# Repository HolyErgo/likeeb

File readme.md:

# LIKEeb

### 36-key split wireless keyboard

## Features
- 3x5 key matrix + 3 thumb keys
- highly staggered columns
- rotated pinky and ring columns
- dactyl-like curved columns (not rows)
- Xiao BLE wireless controllers
- hotswap Gateron and Choc V2 switches
- 400mAh battery lasts month or more
- integrated 50-mm magnetic ring
- 2-color case
- magnetic spacer
- no RGB, ergonomics only
- [height-adapted DES-profile keycaps](https://github.com/HolyErgo/DES-MX-low-profile)
- [ZMK firmware](https://github.com/HolyErgo/zmk-likeeb)

## Comfort and Ergonomics

The curve, stagger, and rotation of the columns provide maximum ergonomics. All keys are easily pressed without moving the base of the hand (for M-L hand size).

Thanks to the low profile, the keyboard is comfortable to use without wrist rests and tents.

Placing the controller under the palm allows for convenient keyboard positioning on either side of a laptop, even on a small café table.

400mAh battery lasts more than a month. I haven’t been able to measure exactly how long, because I always forget when I last charged it :) With the new ZMK firmware using Bluetooth Low Energy protocol, one charge might last 3-4 months.

## Integrated Magnetic Ring

It’s very convenient for designing various mounts. You only need to attach a 0.6mm thick metal ring to the mount. Compared to a magnetic mount, this ring is very thin and much cheaper.

For example, I made a mount for an IKEA garden chair that is only 2mm thick. I simply attached it to the armrest of the chair and created a comfortable workspace: [IKEA chair holder.stl](./case/rev2.0/IKEA%20chair%20holder.stl)

## Convenient Transportation

The magnetic spacer connects two halves of the keyboard and protects the keys from accidental presses. I don’t even turn off the keyboard when I put it in my backpack.

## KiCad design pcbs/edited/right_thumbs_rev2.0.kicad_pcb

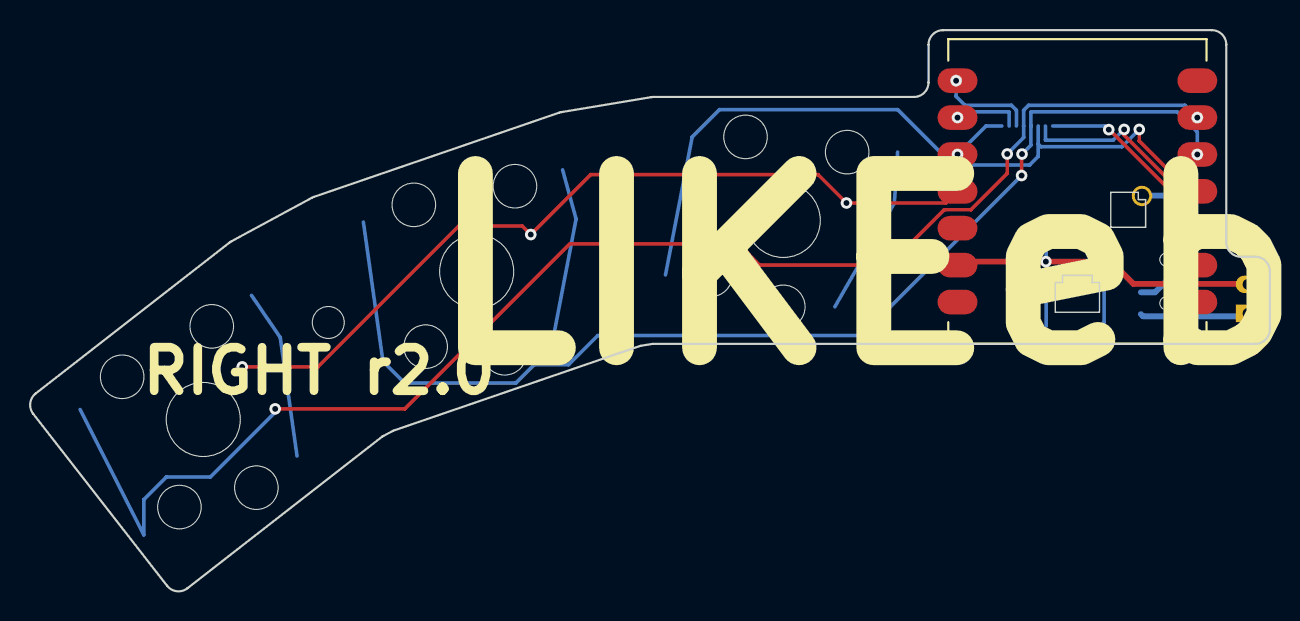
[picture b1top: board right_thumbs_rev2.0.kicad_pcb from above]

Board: 2 copper layers, 85.4 x 38.6 mm, 8 parts (1 on the bottom side), 12 nets.

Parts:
B1: SW_TACT_ALPS_SKQGABE010
BAT1: BatteryPad
S1, S2, S3: KS33PG1353
_1: Seeeduino XIAO nRF52840
_2: HKW FPC Socket
_3: MountingHole_2.2mm_M2_Pad_Via

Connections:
C6: S3.1, S3.2, _1.6, _2.4
C7: S2.1, S2.2, _1.5, _2.5
C8: S1.1, S1.2, _1.4, _2.6
C9: _1.3, _2.7
C10: _1.2, _2.8
GND: B1.1, BAT1.2, _1.13
R1: _1.8, _2.3
R2: _1.9, _2.2
R3: _1.10, _2.1
S1_s2d: S1.1, S1.2
S2_s2d: S2.1, S2.2
S3_s2d: S3.1, S3.2

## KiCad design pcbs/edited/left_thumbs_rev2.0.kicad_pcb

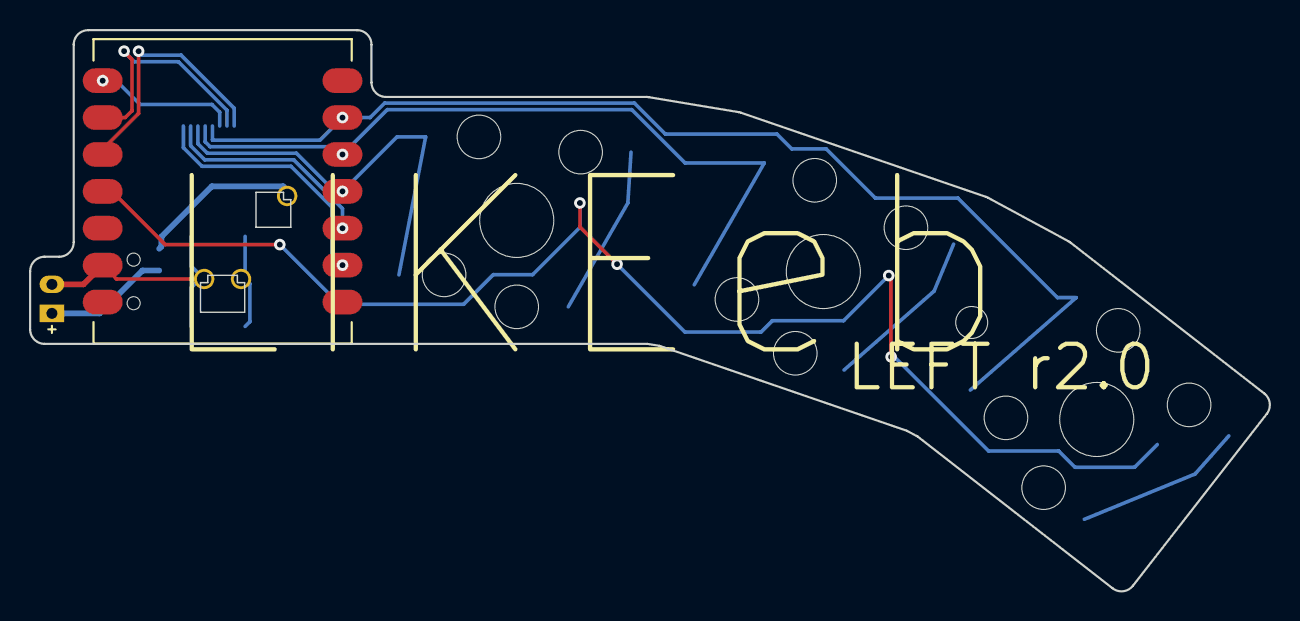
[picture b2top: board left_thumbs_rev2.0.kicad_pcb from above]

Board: 2 copper layers, 85.4 x 38.6 mm, 8 parts (1 on the bottom side), 12 nets.

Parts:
B1: SW_TACT_ALPS_SKQGABE010
BAT1: BatteryPad
S1, S2, S3: KS33PG1353
_1: Seeeduino XIAO nRF52840
_2: HKW FPC Socket
_3: MountingHole_2.2mm_M2_Pad_Via

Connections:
C1: _1.2, _2.1
C2: _1.3, _2.2
C3: S1.1, S1.2, _1.4, _2.3
C4: S2.1, S2.2, _1.5, _2.4
C5: S3.1, S3.2, _1.6, _2.5
GND: B1.1, BAT1.2, _1.13
R1: _1.8, _2.6
R2: _1.9, _2.7
R3: _1.10, _2.8
S1_s2d: S1.1, S1.2
S2_s2d: S2.1, S2.2
S3_s2d: S3.1, S3.2

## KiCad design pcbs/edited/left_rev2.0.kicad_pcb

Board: 2 copper layers, 16 parts (1 on the bottom side), 20 nets.

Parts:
S1, S2, S3, S4, S5, S6, S7, S8, S9, S10, S11, S12, S13, S14, S15: KS33PG1353
_1: HKW FPC Socket

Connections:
C1: S1.1, S1.2, S2.1, S2.2, S3.1, S3.2, _1.8
C2: S4.1, S4.2, S5.1, S5.2, S6.1, S6.2, _1.7
C3: S7.1, S7.2, S8.1, S8.2, S9.1, S9.2, _1.6
C4: S10.1, S10.2, S11.1, S11.2, S15.1, S15.2, _1.5
C4_R2: S15.1, S15.2
C5: S12.1, S12.2, S13.1, S13.2, S14.1, S14.2, _1.4
S1_s2d: S1.1, S1.2
S2_s2d: S2.1, S2.2
S3_s2d: S3.1, S3.2
S4_s2d: S4.1, S4.2
S5_s2d: S5.1, S5.2
S6_s2d: S6.1, S6.2
S7_s2d: S7.1, S7.2
S8_s2d: S8.1, S8.2
S9_s2d: S9.1, S9.2
S10_s2d: S10.1, S10.2
S11_s2d: S11.1, S11.2
S12_s2d: S12.1, S12.2
S13_s2d: S13.1, S13.2
S14_s2d: S14.1, S14.2

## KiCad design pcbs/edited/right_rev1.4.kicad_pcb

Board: 2 copper layers, 16 parts (1 on the bottom side), 5 nets.

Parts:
S1, S2, S3, S4, S5, S6, S7, S8, S9, S10, S11, S12, S13, S14, S15: PG1353
_1: HKW FPC Socket

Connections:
C6: S13.1, S14.1, S15.1, _1.5
C7: S10.1, S11.1, S12.1, _1.4
C8: S7.1, S8.1, S9.1, _1.3
C9: S4.1, S5.1, S6.1, _1.2
C10: S1.1, S2.1, S3.1, _1.1

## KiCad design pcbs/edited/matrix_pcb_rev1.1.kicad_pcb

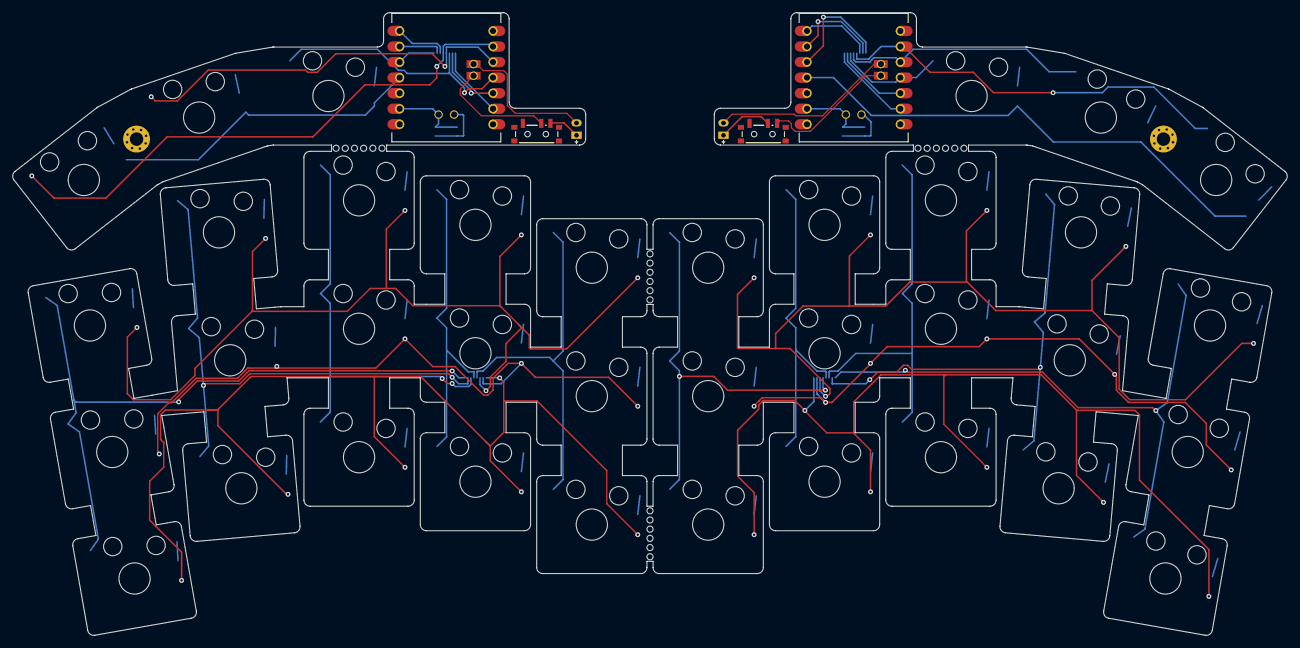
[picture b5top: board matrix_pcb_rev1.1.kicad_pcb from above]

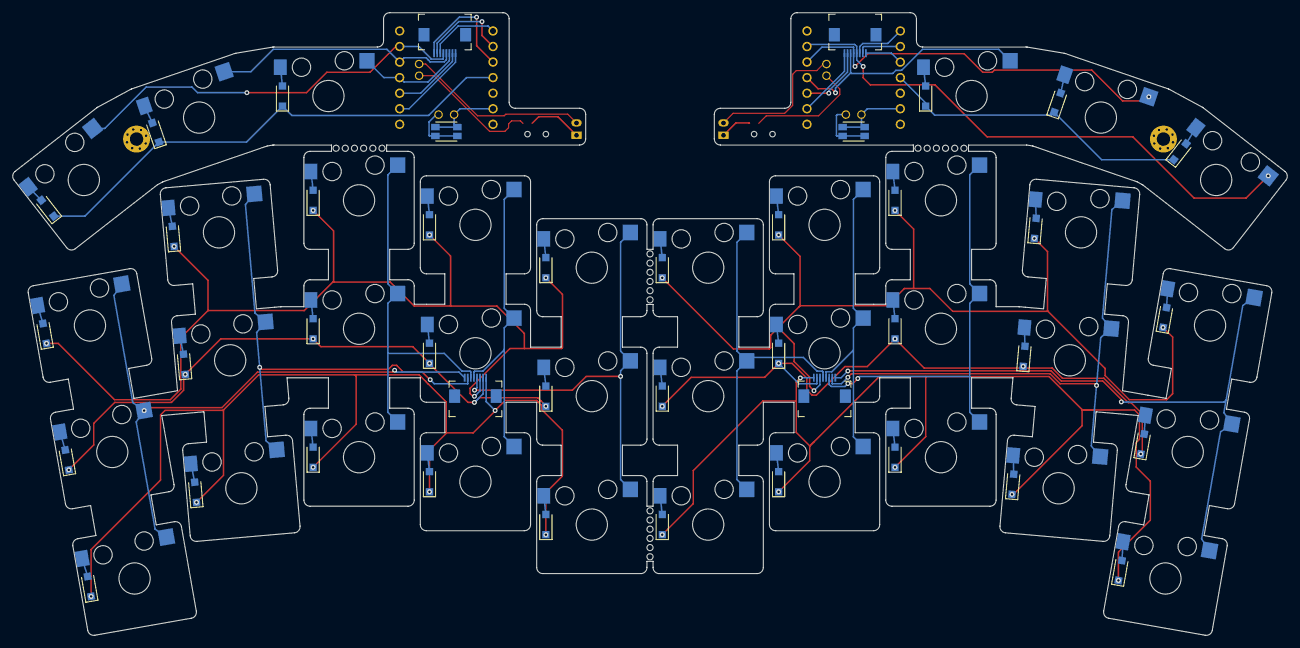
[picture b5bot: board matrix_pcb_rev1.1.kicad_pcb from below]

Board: 2 copper layers, 208.1 x 101.6 mm, 52 parts (4 on the bottom side), 18 nets.

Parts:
BAT1, BAT2: BatteryPad
S1, S2, S3, S4, S5, S6, S7, S8, S9, S10, S11, S12, S13, S14, S15, S16, S17, S18, S19, S20, S21, S22, S23, S24, S25, S26, S27, S28, S29, S30, S31, S32, S33, S34, S35, S36: GateronLowProfileSwitch
SW1, SW3: power_switch
SW2, SW4: sw_reset_side
_11, _13, _15, _17: HKWClamshellSocket
_14, _18: MountingHole_2.2mm_M2_Pad_Via
_19, _20, _21, _22: Bridge holes 6 x 1mm

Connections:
BAT_P: BAT1.1, SW1.2
C1: S1.1, S2.1, S3.1, _11.8
C2: S4.1, S5.1, S6.1, _11.7
C3: S7.1, S8.1, S9.1, _11.6
C4: S10.1, S11.1, S12.1, _11.5
C5: S13.1, S14.1, S15.1, _11.4
C6: S28.1, S29.1, S30.1, _15.5
C7: S25.1, S26.1, S27.1, _15.4
C8: S22.1, S23.1, S24.1, _15.3
C9: S19.1, S20.1, S21.1, _15.2
C10: S16.1, S17.1, S18.1, _15.1
CT3: S31.1, _13.3
CT4: S32.1, _13.4
CT5: S33.1, _13.5
CT6: S36.1, _17.4
CT7: S35.1, _17.5
CT8: S34.1, _17.6
RBAT_P: BAT2.1, SW3.3

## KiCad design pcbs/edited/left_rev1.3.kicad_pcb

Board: 2 copper layers, 16 parts (1 on the bottom side), 5 nets.

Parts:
S1, S2, S3, S4, S5, S6, S7, S8, S9, S10, S11, S12, S13, S14, S15: GateronLowProfileSwitch
_1: HKW FPC Socket

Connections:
C1: S1.1, S2.1, S3.1, _1.8
C2: S4.1, S5.1, S6.1, _1.7
C3: S7.1, S8.1, S9.1, _1.6
C4: S10.1, S11.1, S12.1, _1.5
C5: S13.1, S14.1, S15.1, _1.4

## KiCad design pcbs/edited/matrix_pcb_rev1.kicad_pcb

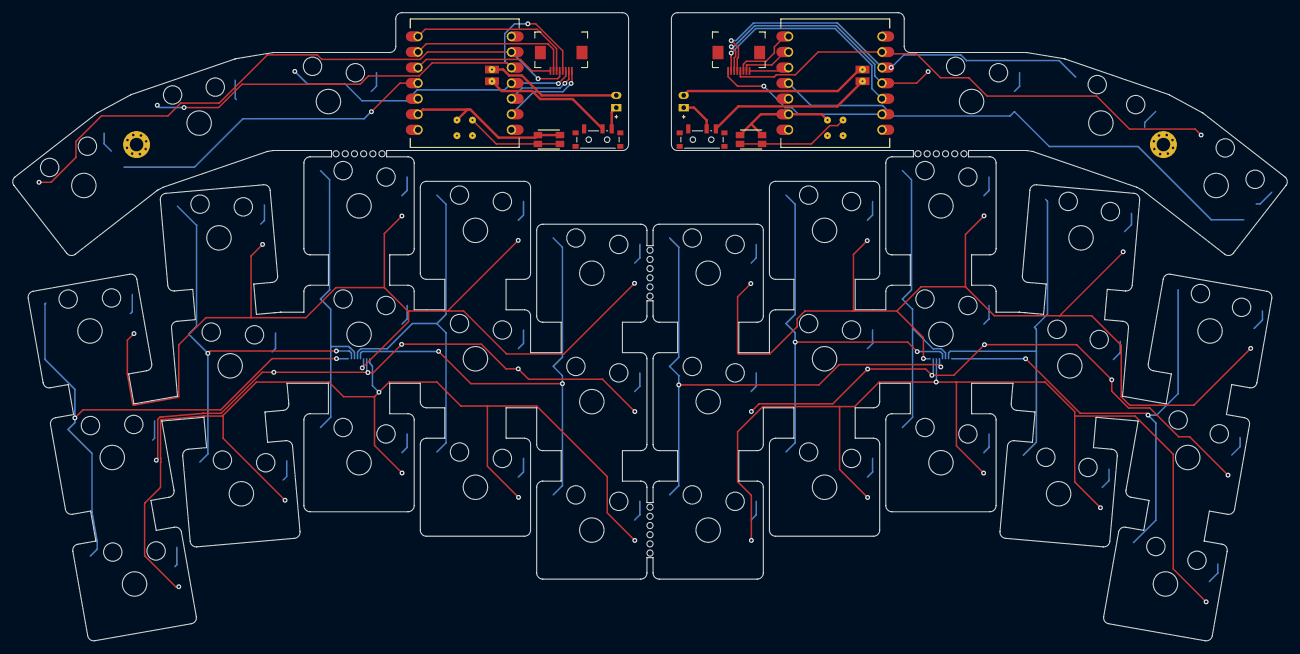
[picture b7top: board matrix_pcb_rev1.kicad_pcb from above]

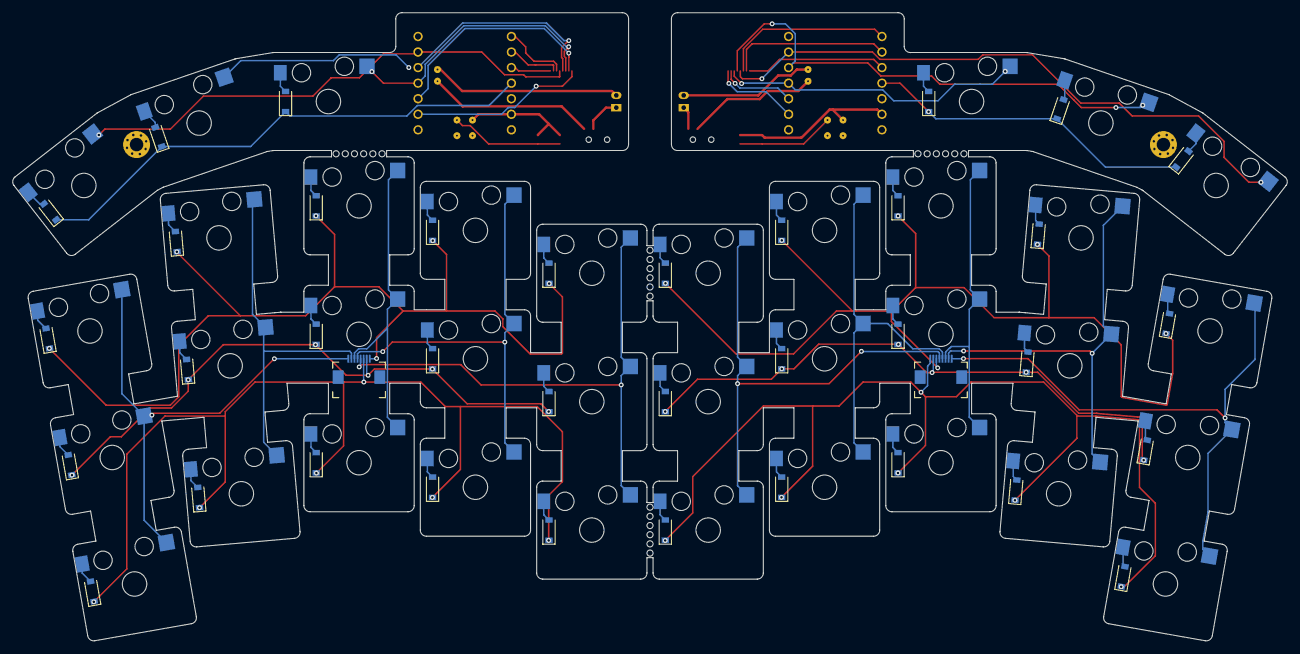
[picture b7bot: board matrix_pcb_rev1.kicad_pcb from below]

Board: 2 copper layers, 208.1 x 102.5 mm, 88 parts (38 on the bottom side), 62 nets.

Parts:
BAT1, BAT2: BatteryPad
D1, D2, D3, D4, D5, D6, D7, D8, D9, D10, D11, D12, D13, D14, D15, D16, D17, D18, D19, D20, D21, D22, D23, D24, D25, D26, D27, D28, D29, D30, D31, D32, D33, D34, D35, D36: SmdDiode
S1, S2, S3, S4, S5, S6, S7, S8, S9, S10, S11, S12, S13, S14, S15, S16, S17, S18, S19, S20, S21, S22, S23, S24, S25, S26, S27, S28, S29, S30, S31, S32, S33, S34, S35, S36: MX
SW1, SW3: power_switch
SW2, SW4: sw_reset_side
_1, _3, _5, _7: HKWClamshellSocket
_4, _8: MountingHole_2.2mm_M2_Pad_Via
_9, _10, _11, _12: Bridge holes 6 x 1mm

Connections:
BAT_P: BAT1.1, SW1.2
C1: S1.1, S2.1, S3.1, _1.8
C2: S4.1, S5.1, S6.1, _1.7
C3: S7.1, S8.1, S9.1, _1.6
C4: S10.1, S11.1, S12.1, _1.5
C5: S13.1, S14.1, S15.1, _1.4
C6: S28.1, S29.1, S30.1, _5.5
C7: S25.1, S26.1, S27.1, _5.4
C8: S22.1, S23.1, S24.1, _5.3
C9: S19.1, S20.1, S21.1, _5.2
C10: S16.1, S17.1, S18.1, _5.1
CT3: S31.1, _3.3
CT4: S32.1, _3.4
CT5: S33.1, _3.5
CT6: S36.1, _7.4
CT7: S35.1, _7.5
CT8: S34.1, _7.6
RBAT_P: BAT2.1, SW3.3
RL1: D2.1, D5.1, D8.1, D11.1, D14.1, _1.3
RL2: D1.1, D4.1, D7.1, D10.1, D13.1, _1.2
RL3: D3.1, D6.1, D9.1, D12.1, D15.1, _1.1
RLT4: D31.1, D32.1, D33.1
RR1: D17.1, D20.1, D23.1, D26.1, D29.1, _5.8
RR2: D16.1, D19.1, D22.1, D25.1, D28.1, _5.7
RR3: D18.1, D21.1, D24.1, D27.1, D30.1, _5.6
RRT4: D34.1, D35.1, D36.1
far_only: D33.2, S33.2
home_only: D32.2, S32.2
index_bottom: D12.2, S12.2
index_home: D10.2, S10.2
index_top: D11.2, S11.2
inner_bottom: D15.2, S15.2
inner_home: D13.2, S13.2
inner_top: D14.2, S14.2
middle_bottom: D9.2, S9.2
middle_home: D7.2, S7.2
middle_top: D8.2, S8.2
mirror_far_only: D36.2, S36.2
mirror_home_only: D35.2, S35.2
mirror_index_bottom: D27.2, S27.2
mirror_index_home: D25.2, S25.2
mirror_index_top: D26.2, S26.2
mirror_inner_bottom: D30.2, S30.2
mirror_inner_home: D28.2, S28.2
mirror_inner_top: D29.2, S29.2
mirror_middle_bottom: D24.2, S24.2
mirror_middle_home: D22.2, S22.2
mirror_middle_top: D23.2, S23.2
mirror_near_only: D34.2, S34.2
mirror_pinky_bottom: D18.2, S18.2
mirror_pinky_home: D16.2, S16.2
mirror_pinky_top: D17.2, S17.2
mirror_ring_bottom: D21.2, S21.2
mirror_ring_home: D19.2, S19.2
mirror_ring_top: D20.2, S20.2
near_only: D31.2, S31.2
pinky_bottom: D3.2, S3.2
pinky_home: D1.2, S1.2
pinky_top: D2.2, S2.2
ring_bottom: D6.2, S6.2
ring_home: D4.2, S4.2
ring_top: D5.2, S5.2

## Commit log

2023-08-26 Revision 1.2 - Socket was moved from middle home to inner home - Vertical column connections became thinner
2023-08-29 Right side with 2mm cols connection
2023-08-29 Some routing "art" for left side
2023-09-01 updated Xiao BLE footprint - added holes and edge cut for NFC underside pads - added edge cut for battery underside pads - added edge cut for RST, CLK and DIO underside pads - side pin holes now are 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
2023-09-01 update to use new Xiao footprint
2023-09-01 refactor footprint's filenames
2023-09-01 fix xiao footprint with correct edge cuts for underside pads
2023-09-01 fix power switch with correct pad's net for backside footprint
2023-09-13 revision 1.3 - 2mm column connections - minimized switch area
2023-09-13 revision 1.3 pcbs
2024-01-08 added cover and keymap
2024-01-11 keymap draw
2024-01-20 cover revision 1.2
2024-01-20 keymap update
2024-01-20 ideas
2024-01-22 diodes group footprint
2024-01-22 mounting hole with optional via
2024-01-22 update thumbs with diode groups, mounting hole without via and moved power and reset switches
2024-01-27 choc V2 footprint
2024-01-27 diode set update with via and smaller width
2024-01-27 choc v2 version
2024-01-27 pcbs rev1.4 with choc v2
2024-09-08 revision 2.0
2024-09-15 Added photos
2024-09-16 readme update
